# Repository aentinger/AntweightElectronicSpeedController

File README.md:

💾 Antweight Electronic Speed Controller (ESC)
==============================================

Firmware of antweight electronic speed controller plus configuration software.

# 📸 Image

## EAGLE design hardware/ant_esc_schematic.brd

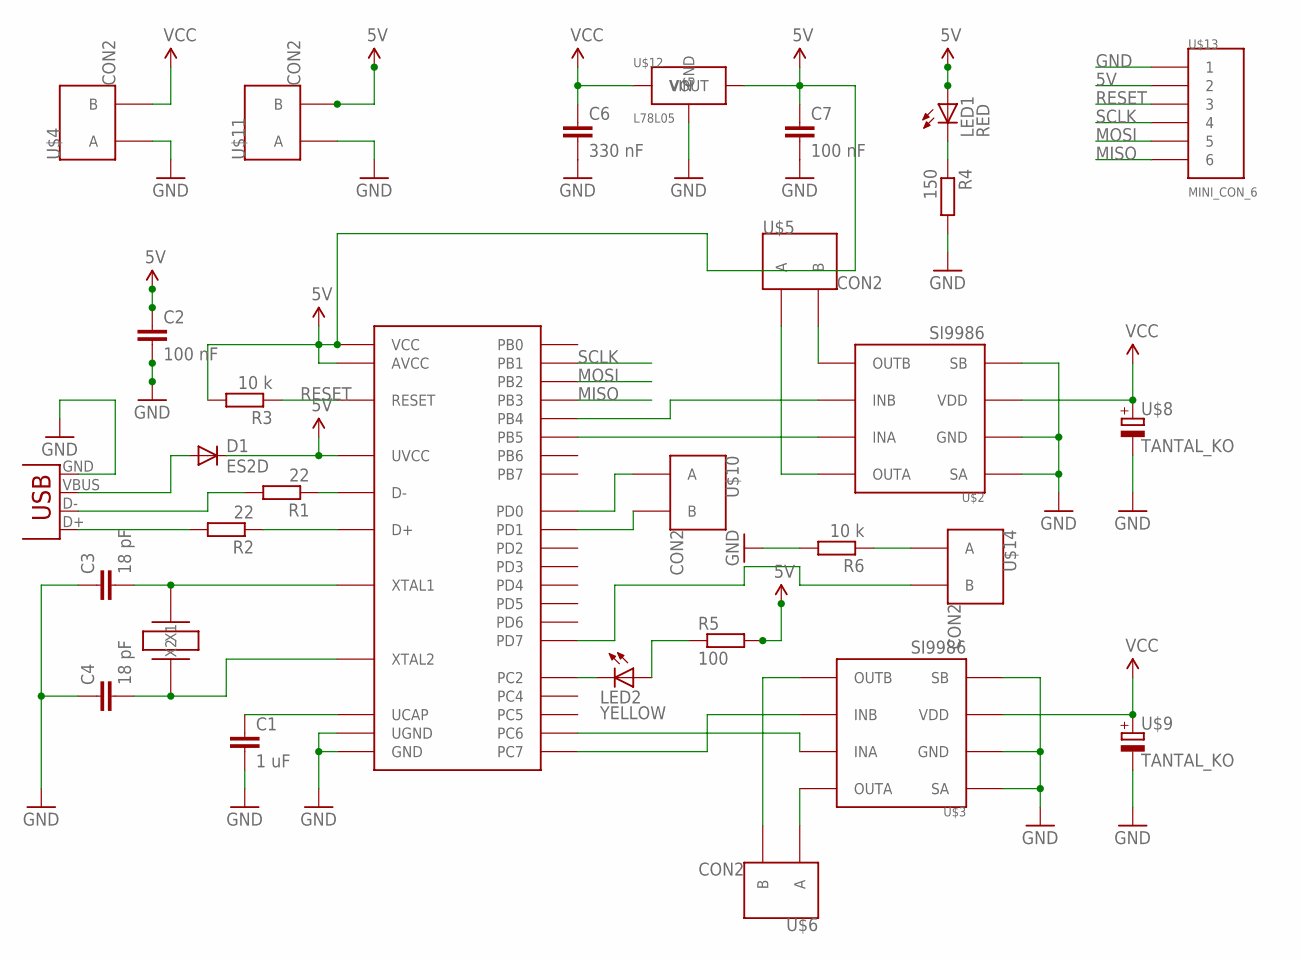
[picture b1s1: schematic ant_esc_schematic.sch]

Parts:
C1: 1 uF; C0805
C2, C7: 100 nF; C0805
C3, C4: 18 pF; C0805
C6: 330 nF; C0805
D1: ES2D; SMB
JP1: USBSMD; USB-MINIB
LED1: RED; CHIPLED_0805
LED2: YELLOW; CHIPLED_0805
R1, R2: 22; M0805
R3, R6: 10 k; M0805
R4: 150; M0805
R5: 100; M0805
U$1: ATMEGA8U2; TQFP32-08
U$2, U$3: SI9986; SOIC8
U$4, U$5, U$6, U$10, U$11, U$14: CON2; 332-02
U$7: 16 MHz; ABM3
U$8, U$9: TANTAL_KO; KEMET_C
U$12: L78L05; SOT89
U$13: MINI_CON_6; MIN_CON_6

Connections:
5V: C2.1, C7.1, D1.C, LED1.A, R3.2, R5.2, U$1.AVCC, U$1.UVCC, U$1.VCC, U$11.2 (B), U$12.VOUT, U$13.2
GND: C1.2, C2.2, C3.1, C4.1, C6.2, C7.2, JP1.GND, R4.2, R6.2, U$1.GND, U$1.UGND, U$2.GND, U$2.SA, U$2.SB, U$3.GND, U$3.SA, U$3.SB, U$4.1 (A), U$8.CATHODE- (-), U$9.CATHODE- (-), U$11.1 (A), U$12.2@1 (GND), U$12.GND, U$13.1
MISO: U$1.PB3, U$13.6
MOSI: U$1.PB2, U$13.5
unnamed: R1.1, U$1.D-
unnamed: R2.1, U$1.D+
unnamed: JP1.D+, R2.2
unnamed: D1.A, JP1.VBUS
unnamed: JP1.D-, R1.2
unnamed: C1.1, U$1.UCAP
unnamed: U$1.PD0, U$10.1 (A)
unnamed: U$1.PB5, U$2.INA
unnamed: U$1.PB4, U$2.INB
unnamed: U$1.PC6, U$3.INA
unnamed: U$1.PC7, U$3.INB
unnamed: U$3.OUTA, U$6.1 (A)
unnamed: U$3.OUTB, U$6.2 (B)
unnamed: U$2.OUTB, U$5.2 (B)
unnamed: U$2.OUTA, U$5.1 (A)
unnamed: LED1.C, R4.1
unnamed: LED2.C, U$1.PC2
unnamed: C4.2, U$1.XTAL2, U$7.X1
unnamed: C3.2, U$1.XTAL1, U$7.X2
unnamed: U$1.PD1, U$10.2 (B)
unnamed: U$1.PD7, U$14.2 (B)
unnamed: LED2.A, R5.1
unnamed: R6.1, U$14.1 (A)
RESET: R3.1, U$1.RESET, U$13.3
SCLK: U$1.PB1, U$13.4
VCC: C6.1, U$2.VDD, U$3.VDD, U$4.2 (B), U$8.ANODE+ (+), U$9.ANODE+ (+), U$12.VIN

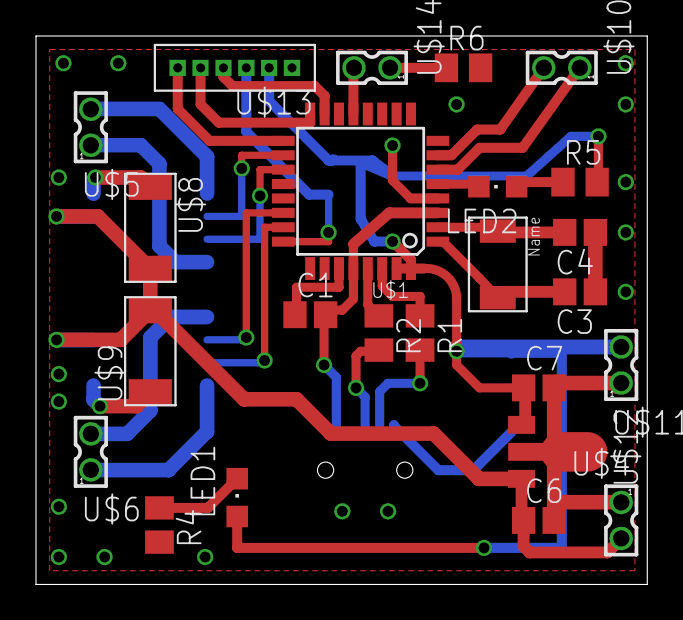
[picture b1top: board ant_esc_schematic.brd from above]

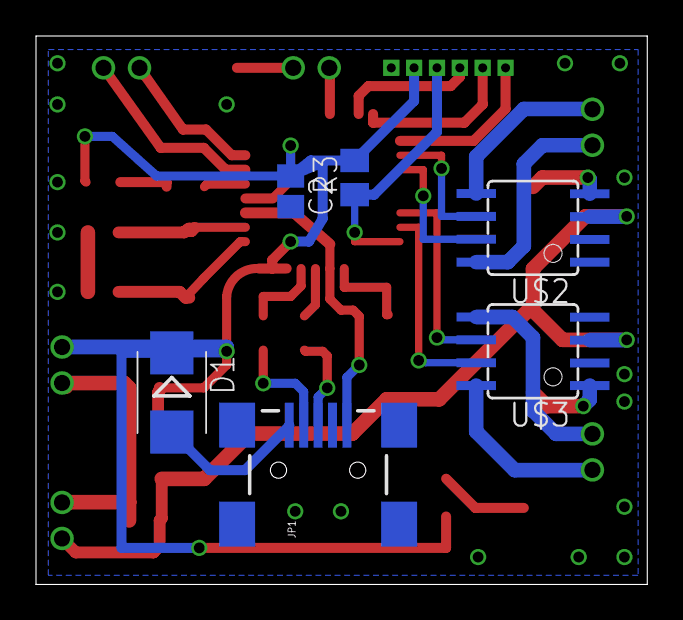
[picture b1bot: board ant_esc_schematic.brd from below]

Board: 2 copper layers, 34.0 x 30.5 mm, 30 parts (6 on the bottom side), 30 nets.

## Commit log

2012-12-07 adding sourcoce for config tool
2012-12-07 changes to cmakelists.txt
2012-12-07 adding configuration functionality for delta mixer code
2012-12-07 correcing minor mistakes
2012-12-07 smaller bugfix
2013-05-15 initial checkin of firmware
2013-05-15 added license message
2013-05-16 comment test
2013-05-16 now the license note is included
2013-05-17 introducing a calibration state for simplicity of understanding the fsm
2013-05-20 added filtering functionality for antweight firmware
2013-05-21 added status led for signalising active and nonactive states
2013-05-21 corrected typo in configuration.cpp
2013-05-28 adding delta mode functionality
2013-05-29 adding calibration of neutral position for delta mode
2013-06-06 resolved conflict
2013-06-06 added support for delta mixer configuration
2013-06-06 small bugfixes while testing
2013-06-07 increased sesibility of failsafe
2013-06-07 added compiled binaries for config tool
2013-06-07 adding updated cdc bootloader
2013-06-08 latest bootloader version
2017-06-27 Adding hardware + images
2025-03-26 Add BOM.
2025-03-26 Adding picture of prototype.
2025-03-26 Pretty up README.

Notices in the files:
README.md:
License: CC BY-NC-SA 4.0
parts and their libraries:
SparkFun-Connectors: Licensing: CC v3.0 Share-Alike You are welcome to use this library for commercial purposes.
